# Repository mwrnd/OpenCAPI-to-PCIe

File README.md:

# PCIe to OpenCAPI-Compatible SlimSAS 8x

The [Open Coherant Accelerator Processor Interface (OpenCAPI)](https://opencapi.org/wp-content/uploads/2022/07/OpenCAPI-Overview.pdf) [was a standard](https://opencapi.org/2022/08/09/cxl-consortium-and-opencapi-consortium-sign-letter-of-intent-to-transfer-opencapi-specifications-to-cxl/) that had FPGA-based [Advanced Accelerated Cable (AAC)](https://files.openpower.foundation/s/xSQPe6ypoakKQdq/download/25Gbps-spec-20171108.pdf) [Add-In cards](https://opencapi.org/wp-content/uploads/2018/12/OpenCAPI-Tech-SC18-Exhibitor-Forum.pdf) such as [ADM-PCIE-9H3](https://www.alpha-data.com/product/adm-pcie-9h3/), [ADM-PCIE-9H7](https://www.alpha-data.com/alpha-data-release-adm-pcie-9h7-data-center-board-with-xilinx-virtex-ultrascale-hbm-fpga/), [ADM-PCIE-9V3](https://www.alpha-data.com/product/adm-pcie-9v3/), [ADM-PCIE-9V5](https://www.alpha-data.com/product/adm-pcie-9v5/), [BittWare XUP-VV4](https://www.bittware.com/fpga/xup-vv4/), [BittWare XUP-VVH](https://www.bittware.com/fpga/xup-vvh/), and [Nvidia Innova-2 Flex](https://www.nvidia.com/en-us/networking/ethernet/innova-2-flex/).

The OpenCAPI SlimSAS interface is based on [PCI-Express](https://en.wikipedia.org/wiki/PCI_Express). This project is an adapter capable of connecting such FPGA boards to host systmes with PCIe.

This design uses the OpenCAPI pinout from the [ADM-PCIE-9V5 User Manual (Pg15-19of38)](https://www.alpha-data.com/xml/user_manuals/adm-pcie-9v5%20user%20manual_v1_4.pdf):

The only OpenCAPI board I have to test against is the **Innova-2 MNV303212A-ADLT Rev:A2** and I designed the [OpenCAPI-to-PCIe_for_MNV303212A_RevA2](https://github.com/mwrnd/OpenCAPI-to-PCIe_for_MNV303212A_RevA2) project as an optimized variant of this design for that board.

## Issues when used with the Innova-2 MNV303212A RevA2

The [current v0.2 release](https://github.com/mwrnd/OpenCAPI-to-PCIe/releases/tag/v0.2) of this project worked with the [First Release of the `innova2_xdma_opencapi`](https://github.com/mwrnd/innova2_xdma_opencapi/tree/348716249bafc39514cb1a422a8e2fb5f301f859) project:

```
git clone --revision=348716249bafc39514cb1a422a8e2fb5f301f859 https://github.com/mwrnd/innova2_xdma_opencapi.git
wget https://github.com/mwrnd/innova2_xdma_opencapi/releases/download/v0.1/innova2_xdma_opencapi_bitstream.zip
```

But, it required a [non-standard GTY Channel to PCIe Lane mapping](https://github.com/mwrnd/innova2_xdma_opencapi/blob/348716249bafc39514cb1a422a8e2fb5f301f859/compile.tcl#L14) that Vivado complains about:

The [OpenCAPI-to-PCIe_for_MNV303212A_RevA2](https://github.com/mwrnd/OpenCAPI-to-PCIe_for_MNV303212A_RevA2) project is a version of this adapter optimized for the Innova-2 **MNV303212A Rev:A2**.

# PCB Layout

4-Layer PCB. Inner 2 layers are GND planes. Differential pairs are matched to a length of 65mm +/- 1mm both inter-pair and intra-pair (N-to-P).

# Schematic

## Design Notes

Refer to the [ADM-PCIE-9V5 User Manual (Pg15-19of38)](https://www.alpha-data.com/xml/user_manuals/adm-pcie-9v5%20user%20manual_v1_4.pdf). Useful [High Speed Design presentation](https://www.youtube.com/watch?v=QG0Apol-oj0&t=2832s).

Only a single component is needed for the adapter, a [U10A474200T](https://www.digikey.com/en/products/detail/amphenol-cs-commercial-products/U10A474200T/14632855)/[U10A474240T](https://www.digikey.com/en/products/detail/amphenol-cs-commercial-products/U10A474240T/17066204) SlimSAS 8x Right-Angle SMD Connector.

A SlimSAS 8x Cable such as the [3M 8ES8-1DF21](https://www.trustedparts.com/en/search/8ES8-1DF21)([Datasheet](https://multimedia.3m.com/mws/media/1398233O/3m-slimline-twin-ax-assembly-sff-8654-x8-30awg-78-5100-2665-8.pdf)) is required to use the adapter with an OpenCAPI FPGA Board.

Resistor **R1** is shorted to connect `nPRSNT1` to `nPRSNT2_x8`. The trace can be scratched off and `nPRSNT1` can be connected to `nPRSNT2_x1` or `nPRSNT2_x4` to limit the PCIe lane width.

Additional useful signals from the OpenCAPI connector are routed to a 6x1 0.1" Header ([DigiKey](https://www.digikey.com/en/products/detail/sullins-connector-solutions/PPTC061LFBN-RC/810145)). The pinout matches a [TC74 I2C Temperature Sensor](https://www.microchip.com/en-us/product/tc74) ([DigiKey](https://www.digikey.com/en/products/detail/microchip-technology/TC74A0-3-3VAT/442720)) for testing I2C. I2C pull-ups are on the AAC Add-in card. Note 3.3V is from the PCIe connector. **PRE** is a Presence Detect pin which is connected to GND via a 50-Ohm resistor on the OpenCAPI AAC Add-In card. **RST** is connected to PCIe/OpenCAPI RESET.

### PCB Stackup

I am using values from [JLCPCB](https://jlcpcb.com/capabilities/pcb-capabilities).

### Trace Impedance Control

OpenCAPI uses 85ohm impedance cables. I played with the values until I got the loosest differential pair coupling that is manufacturable with larger tolerances.

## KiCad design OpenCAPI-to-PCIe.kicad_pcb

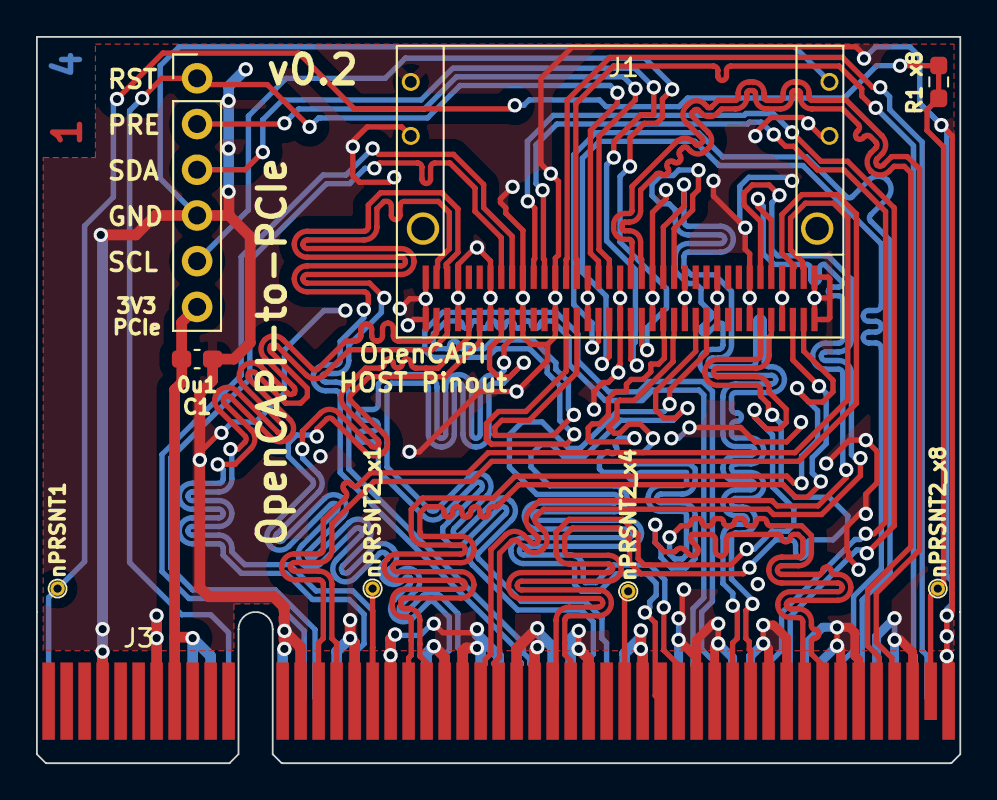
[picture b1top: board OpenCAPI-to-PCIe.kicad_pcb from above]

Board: 4 copper layers, 51.3 x 40.4 mm, 9 parts (0 on the bottom side), 43 nets.

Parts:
C1: 0u1; C_0603_1608Metric_Pad1.08x0.95mm_HandSolder
J1: OpenCAPI_AAC_Host; SlimSAS_8x_RA_U10-A474
J2: Conn_01x06; PinHeader_1x06_P2.54mm_Vertical
J3: Bus_PCI_Express_x8; BUS_PCIexpress_x8
R1: x8; R_0603_1608Metric_Pad0.98x0.95mm_HandSolder
TP1: nPRSNT1; TestPoint_THTPad_D1.0mm_Drill0.5mm
TP2: nPRSNT2_x1; TestPoint_THTPad_D1.0mm_Drill0.5mm
TP3: nPRSNT2_x4; TestPoint_THTPad_D1.0mm_Drill0.5mm
TP5: nPRSNT2_x8; TestPoint_THTPad_D1.0mm_Drill0.5mm

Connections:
+3.3V: C1.1, J2.6, J3.A9 (+3.3V), J3.A10 (+3.3V), J3.B8 (+3.3V)
GND: C1.2, J1.A1 (GND), J1.A4 (GND), J1.A7 (GND), J1.A10 (GND), J1.A13 (GND), J1.A16 (GND), J1.A19 (GND), J1.A22 (GND), J1.A25 (GND), J1.A28 (GND), J1.A31 (GND), J1.A34 (GND), J1.A37 (GND), J1.B1 (GND), J1.B4 (GND), J1.B7 (GND), J1.B10 (GND), J1.B13 (GND), J1.B16 (GND), J1.B19 (GND), J1.B22 (GND), J1.B25 (GND), J1.B28 (GND), J1.B31 (GND), J1.B34 (GND), J1.B37 (GND), J1.MP (Shield), J2.4, J3.A4 (GND), J3.A12 (GND), J3.A15 (GND), J3.A18 (GND), J3.A20 (GND), J3.A23 (GND), J3.A24 (GND), J3.A27 (GND), J3.A28 (GND), J3.A31 (GND), J3.A34 (GND), J3.A37 (GND), J3.A38 (GND), J3.A41 (GND), J3.A42 (GND), J3.A45 (GND), J3.A46 (GND), J3.A49 (GND), J3.B4 (GND), J3.B7 (GND), J3.B13 (GND), J3.B16 (GND), J3.B18 (GND), J3.B21 (GND), J3.B22 (GND), J3.B25 (GND), J3.B26 (GND), J3.B29 (GND), J3.B32 (GND), J3.B35 (GND), J3.B36 (GND), J3.B39 (GND), J3.B40 (GND), J3.B43 (GND), J3.B44 (GND), J3.B47 (GND), J3.B49 (GND)
unnamed: J3.A1 (~PRSNT1), J3.B48 (~PRSNT2), R1.1, R1.2, TP1.1, TP5.1
unnamed: J3.B17 (~PRSNT2), TP2.1
unnamed: J3.B31 (~PRSNT2), TP3.1
PRE_DETECT: J1.A20 (PRE_DETECT), J2.2
REFCLK_N: J1.A30 (REFCLK_N), J3.A14 (REFCLK-)
REFCLK_P: J1.A29 (REFCLK_P), J3.A13 (REFCLK+)
Rx0_N: J1.B36 (Rx0_N), J3.A17 (PERn0)
Rx0_P: J1.B35 (Rx0_P), J3.A16 (PERp0)
Rx1_N: J1.B33 (Rx1_N), J3.A22 (PERn1)
Rx1_P: J1.B32 (Rx1_P), J3.A21 (PERp1)
Rx2_N: J1.A36 (Rx2_N), J3.A26 (PERn2)
Rx2_P: J1.A35 (Rx2_P), J3.A25 (PERp2)
Rx3_N: J1.B30 (Rx3_N), J3.A30 (PERn3)
Rx3_P: J1.B29 (Rx3_P), J3.A29 (PERp3)
Rx4_N: J1.B24 (Rx4_N), J3.A36 (PERn4)
Rx4_P: J1.B23 (Rx4_P), J3.A35 (PERp4)
Rx5_N: J1.A27 (Rx5_N), J3.A40 (PERn5)
Rx5_P: J1.A26 (Rx5_P), J3.A39 (PERp5)
Rx6_N: J1.B21 (Rx6_N), J3.A44 (PERn6)
Rx6_P: J1.B20 (Rx6_P), J3.A43 (PERp6)
Rx7_N: J1.A24 (Rx7_N), J3.A48 (PERn7)
Rx7_P: J1.A23 (Rx7_P), J3.A47 (PERp7)
SCL: J1.B17 (I2C_SCL), J2.5
SDA: J1.B18 (I2C_SDA), J2.3
Tx0_N: J1.A3 (Tx0_N), J3.B15 (PETn0)
Tx0_P: J1.A2 (Tx0_P), J3.B14 (PETp0)
Tx1_N: J1.B3 (Tx1_N), J3.B20 (PETn1)
Tx1_P: J1.B2 (Tx1_P), J3.B19 (PETp1)
Tx2_N: J1.A6 (Tx2_N), J3.B24 (PETn2)
Tx2_P: J1.A5 (Tx2_P), J3.B23 (PETp2)
Tx3_N: J1.B6 (Tx3_N), J3.B28 (PETn3)
Tx3_P: J1.B5 (Tx3_P), J3.B27 (PETp3)
Tx4_N: J1.B12 (Tx4_N), J3.B34 (PETn4)
Tx4_P: J1.B11 (Tx4_P), J3.B33 (PETp4)
Tx5_N: J1.A15 (Tx5_N), J3.B38 (PETn5)
Tx5_P: J1.A14 (Tx5_P), J3.B37 (PETp5)
Tx6_N: J1.B15 (Tx6_N), J3.B42 (PETn6)
Tx6_P: J1.B14 (Tx6_P), J3.B41 (PETp6)
Tx7_N: J1.A18 (Tx7_N), J3.B46 (PETn7)
Tx7_P: J1.A17 (Tx7_P), J3.B45 (PETp7)
nPERST: J1.A21 (INT_RST), J2.1, J3.A11 (~PERST)

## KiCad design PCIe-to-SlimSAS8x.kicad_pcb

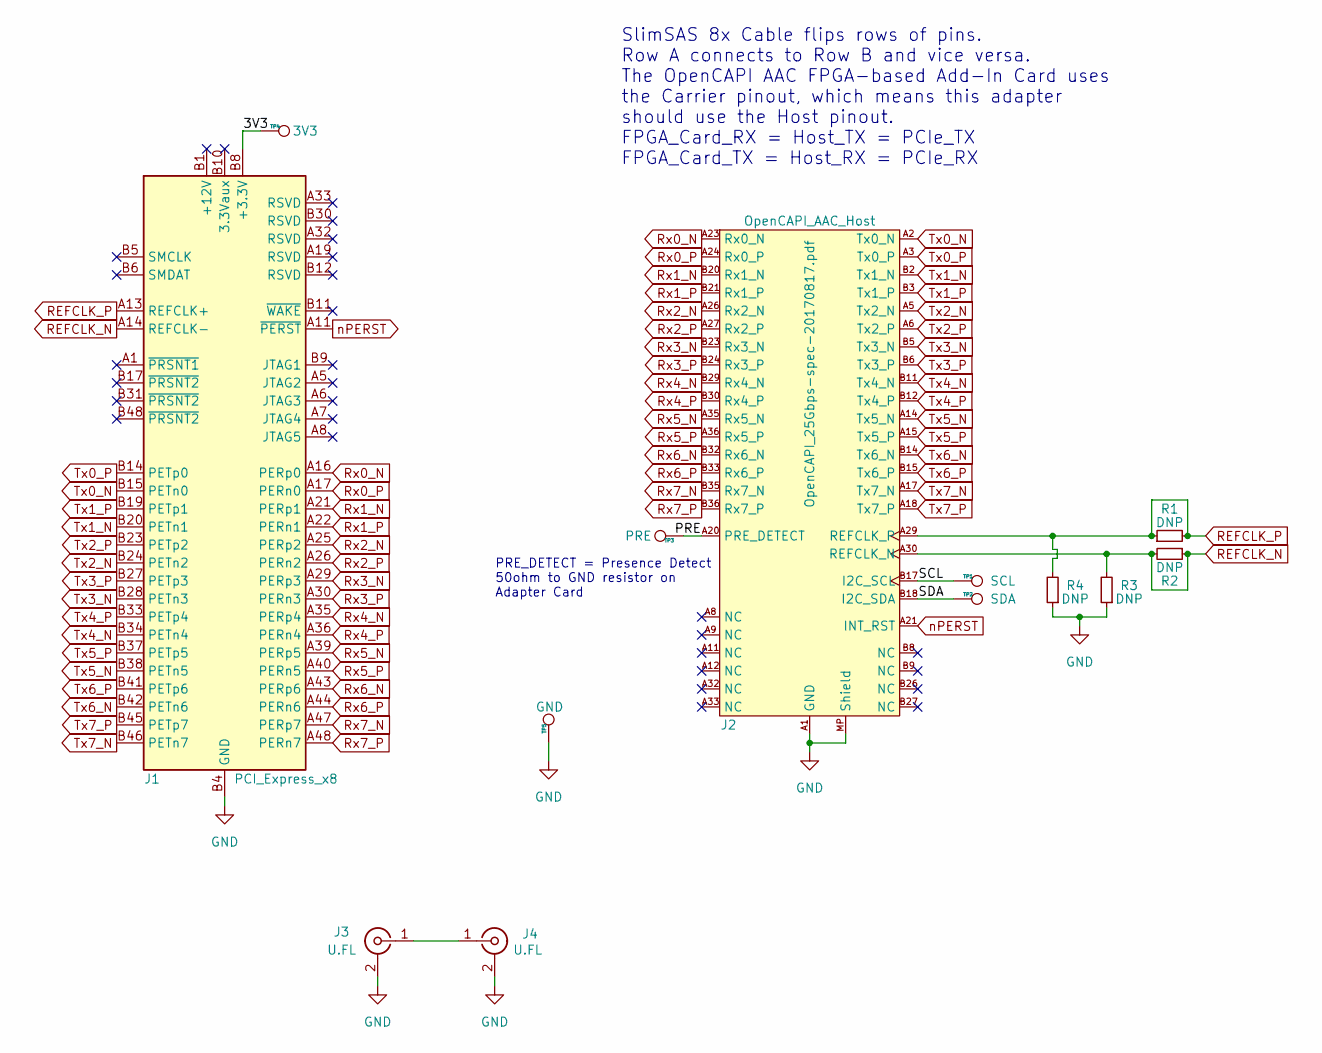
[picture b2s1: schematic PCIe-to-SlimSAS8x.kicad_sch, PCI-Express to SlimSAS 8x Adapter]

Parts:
J1: PCI_Express_x8; BUS_PCIexpress_x8
J2: OpenCAPI_AAC_Host; SlimSAS_8x_RA_U10-A474
J3, J4: U.FL; U.FL_Hirose_U.FL-R-SMT-1_Vertical
R1, R2, R3, R4: DNP; R_0603_1608Metric
TP1: SCL; PinHeader_1x01_P2.54mm_Vertical
TP2: SDA; PinHeader_1x01_P2.54mm_Vertical
TP3: PRE; PinHeader_1x01_P2.54mm_Vertical
TP4: 3V3; PinHeader_1x01_P2.54mm_Vertical
TP5: GND; PinHeader_1x01_P2.54mm_Vertical

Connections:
/3V3: J1.A9 (+3.3V), J1.A10 (+3.3V), J1.B8 (+3.3V), TP4.1
/PRE: J2.A20 (PRE_DETECT), TP3.1
/SCL: J2.B17 (I2C_SCL), TP1.1
/SDA: J2.B18 (I2C_SDA), TP2.1
GND: J1.A4 (GND), J1.A12 (GND), J1.A15 (GND), J1.A18 (GND), J1.A20 (GND), J1.A23 (GND), J1.A24 (GND), J1.A27 (GND), J1.A28 (GND), J1.A31 (GND), J1.A34 (GND), J1.A37 (GND), J1.A38 (GND), J1.A41 (GND), J1.A42 (GND), J1.A45 (GND), J1.A46 (GND), J1.A49 (GND), J1.B4 (GND), J1.B7 (GND), J1.B13 (GND), J1.B16 (GND), J1.B18 (GND), J1.B21 (GND), J1.B22 (GND), J1.B25 (GND), J1.B26 (GND), J1.B29 (GND), J1.B32 (GND), J1.B35 (GND), J1.B36 (GND), J1.B39 (GND), J1.B40 (GND), J1.B43 (GND), J1.B44 (GND), J1.B47 (GND), J1.B49 (GND), J2.A1 (GND), J2.A4 (GND), J2.A7 (GND), J2.A10 (GND), J2.A13 (GND), J2.A16 (GND), J2.A19 (GND), J2.A22 (GND), J2.A25 (GND), J2.A28 (GND), J2.A31 (GND), J2.A34 (GND), J2.A37 (GND), J2.B1 (GND), J2.B4 (GND), J2.B7 (GND), J2.B10 (GND), J2.B13 (GND), J2.B16 (GND), J2.B19 (GND), J2.B22 (GND), J2.B25 (GND), J2.B28 (GND), J2.B31 (GND), J2.B34 (GND), J2.B37 (GND), J2.MP (Shield), J3.2 (Ext), J4.2 (Ext), R3.1, R4.1, TP5.1
unnamed: J3.1 (In), J4.1 (In)
REFCLK_N: J1.A14 (REFCLK-), J2.A30 (REFCLK_N), R2.1, R2.2, R3.2
REFCLK_P: J1.A13 (REFCLK+), J2.A29 (REFCLK_P), R1.1, R1.2, R4.2
Rx0_N: J1.A16 (PERp0), J2.A23 (Rx0_N)
Rx0_P: J1.A17 (PERn0), J2.A24 (Rx0_P)
Rx1_N: J1.A21 (PERp1), J2.B20 (Rx1_N)
Rx1_P: J1.A22 (PERn1), J2.B21 (Rx1_P)
Rx2_N: J1.A25 (PERp2), J2.A26 (Rx2_N)
Rx2_P: J1.A26 (PERn2), J2.A27 (Rx2_P)
Rx3_N: J1.A29 (PERp3), J2.B23 (Rx3_N)
Rx3_P: J1.A30 (PERn3), J2.B24 (Rx3_P)
Rx4_N: J1.A35 (PERp4), J2.B29 (Rx4_N)
Rx4_P: J1.A36 (PERn4), J2.B30 (Rx4_P)
Rx5_N: J1.A39 (PERp5), J2.A35 (Rx5_N)
Rx5_P: J1.A40 (PERn5), J2.A36 (Rx5_P)
Rx6_N: J1.A43 (PERp6), J2.B32 (Rx6_N)
Rx6_P: J1.A44 (PERn6), J2.B33 (Rx6_P)
Rx7_N: J1.A47 (PERp7), J2.B35 (Rx7_N)
Rx7_P: J1.A48 (PERn7), J2.B36 (Rx7_P)
Tx0_N: J1.B15 (PETn0), J2.A2 (Tx0_N)
Tx0_P: J1.B14 (PETp0), J2.A3 (Tx0_P)
Tx1_N: J1.B20 (PETn1), J2.B2 (Tx1_N)
Tx1_P: J1.B19 (PETp1), J2.B3 (Tx1_P)
Tx2_N: J1.B24 (PETn2), J2.A5 (Tx2_N)
Tx2_P: J1.B23 (PETp2), J2.A6 (Tx2_P)
Tx3_N: J1.B28 (PETn3), J2.B5 (Tx3_N)
Tx3_P: J1.B27 (PETp3), J2.B6 (Tx3_P)
Tx4_N: J1.B34 (PETn4), J2.B11 (Tx4_N)
Tx4_P: J1.B33 (PETp4), J2.B12 (Tx4_P)
Tx5_N: J1.B38 (PETn5), J2.A14 (Tx5_N)
Tx5_P: J1.B37 (PETp5), J2.A15 (Tx5_P)
Tx6_N: J1.B42 (PETn6), J2.B14 (Tx6_N)
Tx6_P: J1.B41 (PETp6), J2.B15 (Tx6_P)
Tx7_N: J1.B46 (PETn7), J2.A17 (Tx7_N)
Tx7_P: J1.B45 (PETp7), J2.A18 (Tx7_P)
nPERST: J1.A11 (~PERST), J2.A21 (INT_RST)

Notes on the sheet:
SlimSAS 8x Cable flips rows of pins. Row A connects to Row B and vice versa. The OpenCAPI AAC FPGA-based Add-In Card uses the Carrier pinout, which means this adapter should use the Host pinout. FPGA_Card_RX = Host_TX = PCIe_TX FPGA_Card_TX = Host_RX = PCIe_RX
PRE_DETECT = Presence Detect 50ohm to GND resistor on Adapter Card

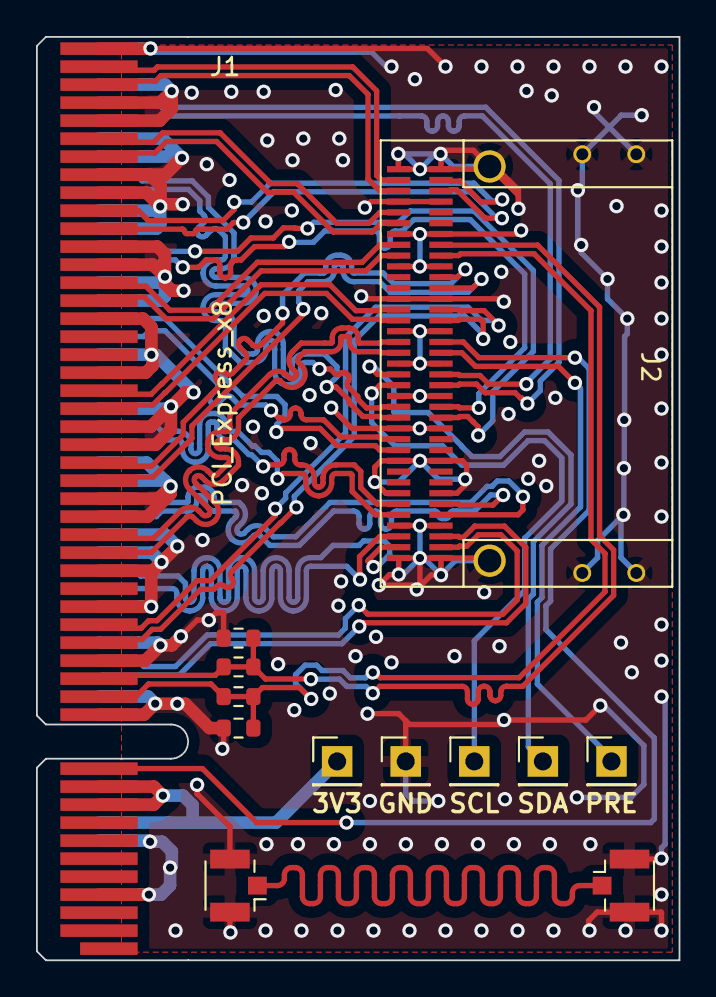
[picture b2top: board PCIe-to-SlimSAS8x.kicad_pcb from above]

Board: 4 copper layers, 35.7 x 51.3 mm, 13 parts (1 on the bottom side), 41 nets.

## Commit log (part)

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2023-01-13 PCB Layout started
2023-01-15 Renamed to PCIe-to-SlimSAS8x
2023-01-15 Initial Layout Complete
2023-01-16 PCB Layout Complete
2023-01-18 Added Microstrip Test Trace
2023-04-30 Rev2 Schematic
2023-06-11 README.md Updated
2023-12-19 Second Revision Completed
2024-03-01 Third Revision
